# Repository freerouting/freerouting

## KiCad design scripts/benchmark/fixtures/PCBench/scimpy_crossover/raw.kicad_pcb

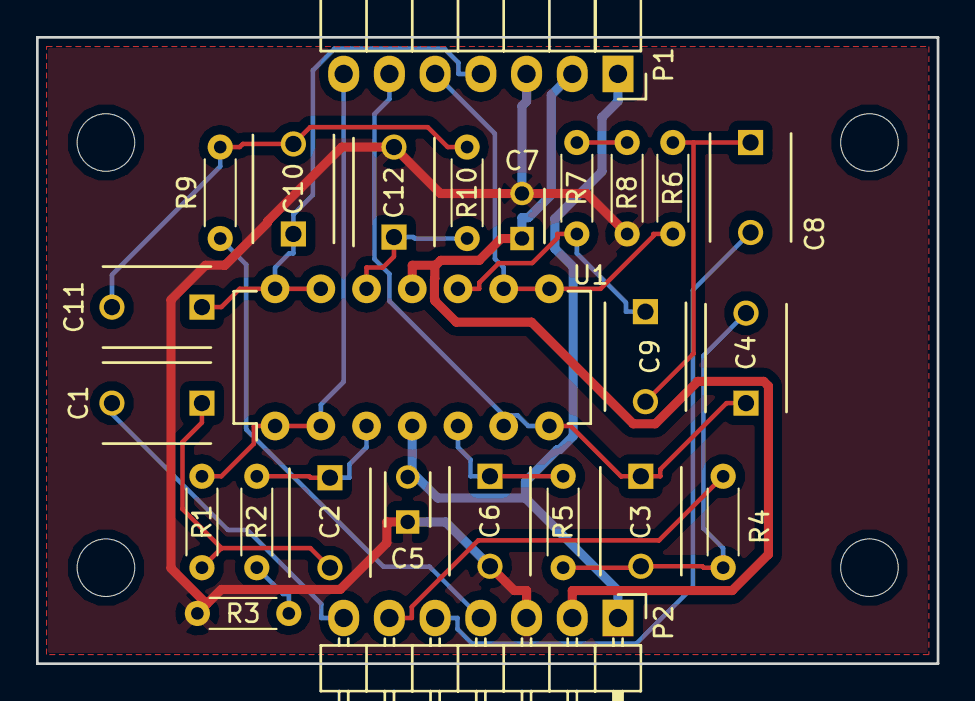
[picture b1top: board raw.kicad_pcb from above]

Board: 2 copper layers, 50.0 x 34.8 mm, 29 parts (0 on the bottom side), 21 nets.

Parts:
C1, C2, C3, C4, C6, C8, C9, C10, C11, C12: 100n; C_Disc_D6_P5
C5, C7: 100n; C_Disc_D3_P2.5
P1: CONN_01X07; Socket_Strip_Angled_1x07
P2: CONN_01X07; Pin_Header_Angled_1x07
R1, R2, R3, R4, R5, R6, R7, R8, R9, R10: R; R_Axial_DIN0204_L3.6mm_D1.6mm_P5.08mm_Horizontal
U1: TL074; DIP-14_W7.62mm
mnt1, mnt2, mnt3, mnt4: MountingHole_3.2mm_M3

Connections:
+15V: C5.2, P1.1, P2.1, U1.4
-15V: C7.1, P1.2, P2.2, U1.11
/left_high_out: P1.5, R6.2, U1.8, U1.9
/left_low_out: C10.1, C11.1, P1.4, U1.13, U1.14
/left_tweeter_ph: C8.2, P2.5
/left_woofer_in: P2.4, R9.1
/right_high_out: P1.7, R1.2, U1.1, U1.2
/right_low_out: C3.1, C4.1, P1.6, U1.6, U1.7
/right_tweeter_ph: C1.2, P2.7
/right_woofer_in: P2.6, R4.1
GND: C5.1, C6.2, C7.2, C12.2, P1.3, P2.3, R3.1, R8.1
unnamed: C1.1, C2.2, R1.1
unnamed: C2.1, R2.2, U1.3
unnamed: C3.2, C4.2, R4.2, R5.2
unnamed: C6.1, R5.1, U1.5
unnamed: C8.1, C9.2, R6.1
unnamed: C9.1, R7.2, U1.10
unnamed: C10.2, C11.2, R9.2, R10.2
unnamed: C12.1, R10.1, U1.12
unnamed: R2.1, R3.2
unnamed: R7.1, R8.2

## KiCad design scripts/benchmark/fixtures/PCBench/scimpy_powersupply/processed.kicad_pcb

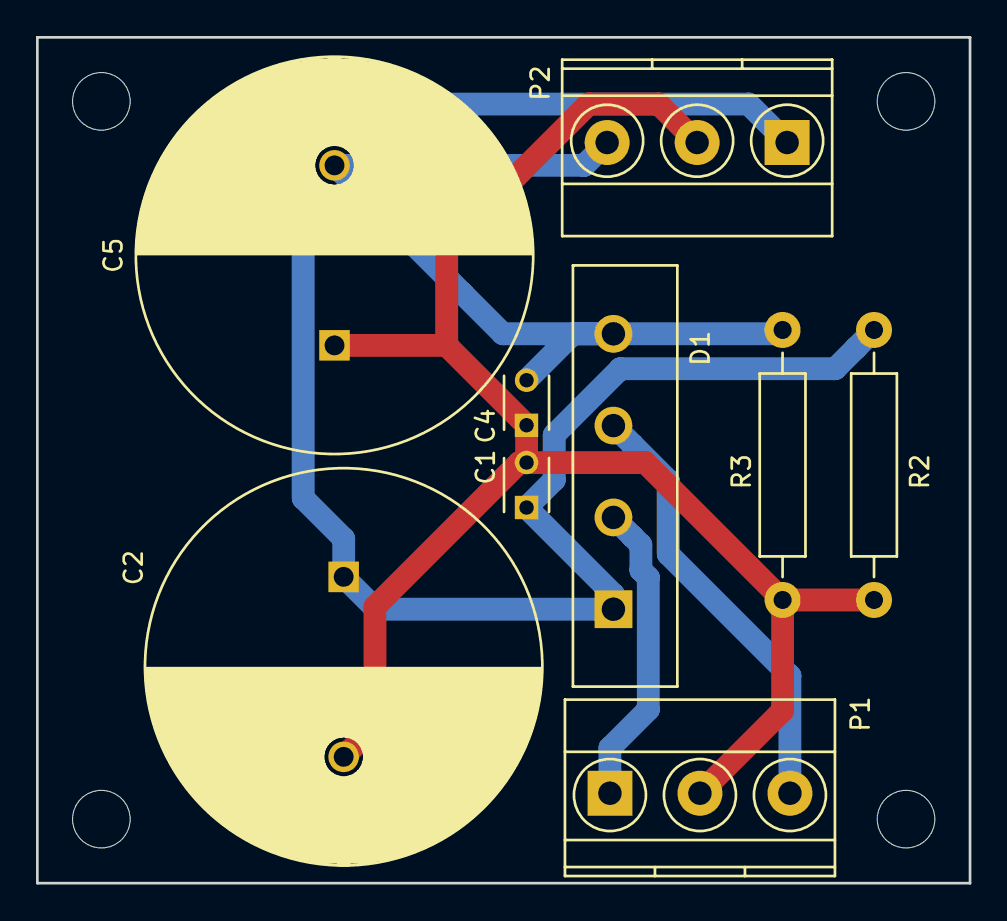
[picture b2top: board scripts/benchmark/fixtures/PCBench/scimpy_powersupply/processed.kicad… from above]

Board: 2 copper layers, 51.8 x 47.0 mm, 9 parts (0 on the bottom side), 5 nets.

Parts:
C1, C4: 100n; C_Disc_D3_P2.5
C2, C5: 6800u; C_Radial_D22_L41_P10
D1: Diode_Bridge; Diode_Bridge_18.5x5.5
P1, P2: CONN_01X03; TerminalBlock_Pheonix_MKDS1.5-3pol
R2, R3: 1K 1W; Resistor_Horizontal_RM15mm

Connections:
+15V: C1.1, C2.1, D1.3, P2.1, R2.1
-15V: C4.2, C5.2, D1.1, P2.3, R3.2
/+12VAC: D1.4, P1.3
/-12VAC: D1.2, P1.1
GND: C1.2, C2.2, C4.1, C5.1, P1.2, P2.2, R2.2, R3.1

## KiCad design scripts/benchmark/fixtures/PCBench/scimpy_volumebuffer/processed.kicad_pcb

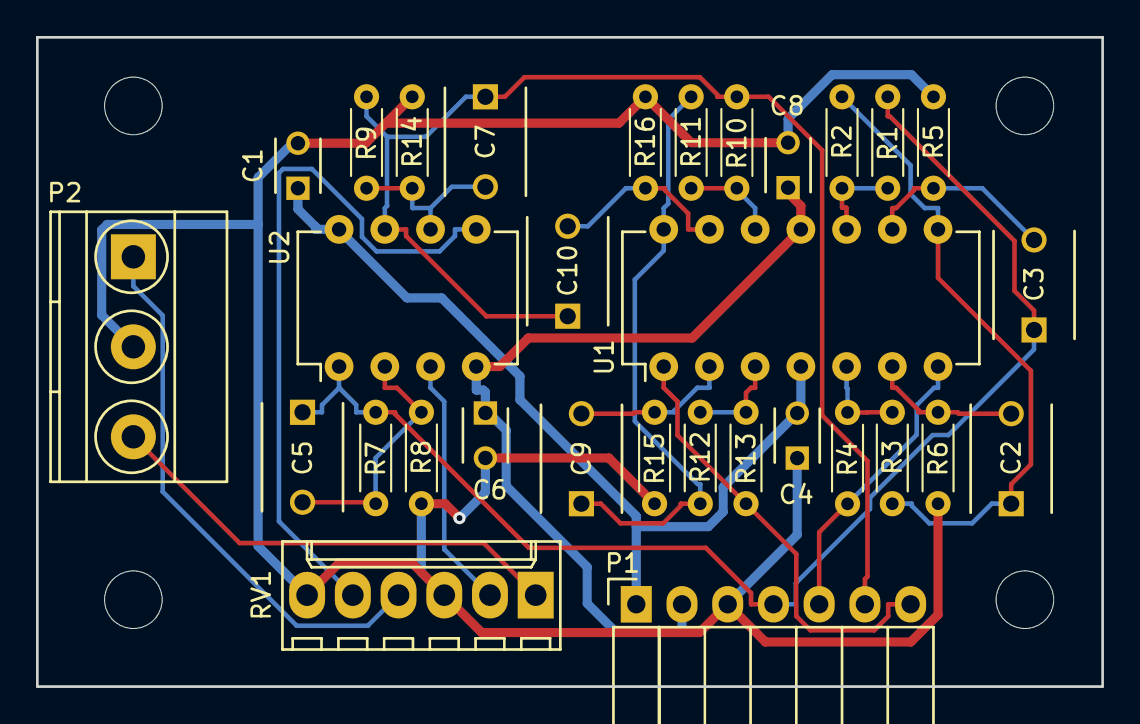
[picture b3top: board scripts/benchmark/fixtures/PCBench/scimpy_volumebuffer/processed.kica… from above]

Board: 2 copper layers, 59.2 x 36.1 mm, 34 parts (0 on the bottom side), 23 nets.

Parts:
C1, C4, C6, C8: 100n; C_Disc_D3_P2.5
C2, C3, C5, C7, C9, C10: 100n; C_Disc_D6_P5
P1: CONN_01X07; Socket_Strip_Angled_1x07
P2: CONN_01X03; TerminalBlock_Pheonix_MKDS1.5-3pol
R1, R2, R3, R4, R10, R11, R12, R13: 2K2; R_Axial_DIN0204_L3.6mm_D1.6mm_P5.08mm_Horizontal
R5, R6, R15, R16: Rph; R_Axial_DIN0204_L3.6mm_D1.6mm_P5.08mm_Horizontal
R7, R9: Rbs1; R_Axial_DIN0204_L3.6mm_D1.6mm_P5.08mm_Horizontal
R8, R14: Rbs2; R_Axial_DIN0204_L3.6mm_D1.6mm_P5.08mm_Horizontal
RV1: DUAL_POT; Molex_KK-6410-06_06x2.54mm_Straight
U1: TL074; DIP-14_W7.62mm
U2: TL072; DIP-8_W7.62mm
mnt1, mnt2, mnt3: MountingHole_3.2mm_M3

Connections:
+15V: C1.1, C4.2, P1.1, U1.4, U2.8
-15V: C6.1, C8.1, P1.2, U1.11, U2.4
/left_bass: C3.1, C5.1, P1.4, R1.2, R7.2, U2.1
/left_in: P2.1, RV1.4
/left_tweet: P1.5, R4.1, U1.7
/right_bass: C7.1, C10.1, P1.6, R9.2, R10.2, U2.7
/right_in: P2.3, RV1.1
/right_tweet: P1.7, R13.1, U1.1
GND: C1.2, C4.1, C6.2, C8.2, P1.3, P2.2, R5.1, R6.1, R8.2, R14.1, R15.1, R16.1, RV1.3, RV1.6
unnamed: C2.1, R2.1, R3.2, U1.8
unnamed: C2.2, R6.2, U1.6
unnamed: C3.2, R5.2, U1.9
unnamed: C5.2, R7.1, R8.1, U2.2
unnamed: C7.2, R9.1, R14.2, U2.6
unnamed: C9.1, R11.1, R12.2, U1.14
unnamed: C9.2, R15.2, U1.2
unnamed: C10.2, R16.2, U1.13
unnamed: R1.1, R2.2, U1.10
unnamed: R3.1, R4.2, U1.5
unnamed: R10.1, R11.2, U1.12
unnamed: R12.1, R13.2, U1.3
unnamed: RV1.2, U2.3
unnamed: RV1.5, U2.5
